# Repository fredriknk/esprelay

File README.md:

# ESPRELAY -_WORK IN PROGRESS-UNTESTED_-

ESP8266 small signal relay module utilizing an [ESP-12-F](./DOCUMENTATION/esp-12f_product_specification_en.pdf) wifi module for communication and MCU, and has two 2.5-25V inputs, and a single 25v, 100ma high speed open drain output through a [TBD062003](./DOCUMENTATION/2304140030_TOSHIBA-TBD62003AFWG_C114084.pdf) DMOS transistor array ic. The three relay outputs are capable of driving around 25V 500ma. 

Thanks to [u/PricelessToolkit/ESPClicker](https://github.com/PricelessToolkit/ESPClicker) for inspiration. If you need a ready to use product you should so head over to his [store](https://www.pricelesstoolkit.com/en/projects/32-espclicker-0741049314405.html) and buy his version.

[Schematic](./DOCUMENTATION/_schematic.pdf)

[Assembly IBOM](https://htmlpreview.github.io/?https://raw.githubusercontent.com/fredriknk/esprelay/main/PRODUCTION/ibom.html)

## Specifications
| **Parameter**   | **Description**                                                     |
|-----------------|---------------------------------------------------------------------|
| _Input voltage_ | 5-15v                               |
| _Current_       | TBD Wifi: ##mA, Radio Off: ##mA, Deep sleep ##uA |  
| _Communication_ | 2.4ghz WIFI, Uart TTL                            |
| _Baudrate_      | 115200                                                              |
| _PCB size_      | 20x65mm                                                             |
| _PCB info_      | 1.6mm FR4, HASL lead free, 4 layer (But works with 2)               |
| _Case size_     | XxXxXmm TBD                                                         |

## Connector
| **Pin**   | **GPIO**|**Description**       |
|------------|-----|-------------------------|
|_vcc_ | -|5-15v |
|_GND_ | -|  Ground  |
|_HI1_ | GPIO4 | 2.5-25v input |
|_HI1_ | GPIO5 | 2.5-25v input |
|_HO1_ | GPIO13 | 25v 100ma open drain output |
|_R1A_ | GPIO12  | Relay 1 COM |
|_R1NC_ | GPIO12 | Relay 1 Normally Closed |
|_R1NO_ | GPIO12 | Relay 1 Normally Open |
|_R2A_ | GPIO12  | Relay 1 COM |
|_R2NO_ | GPIO12 | Relay 1 Normally Open |
|_R3A_ | GPIO12  | Relay 1 COM |
|_R3NO_ | GPIO12 | Relay 1 Normally Open |

## PCB Pictures

## Homeassistant Implementation
TODO

## FIRST PRODUCTION PROTOTYPE
TODO

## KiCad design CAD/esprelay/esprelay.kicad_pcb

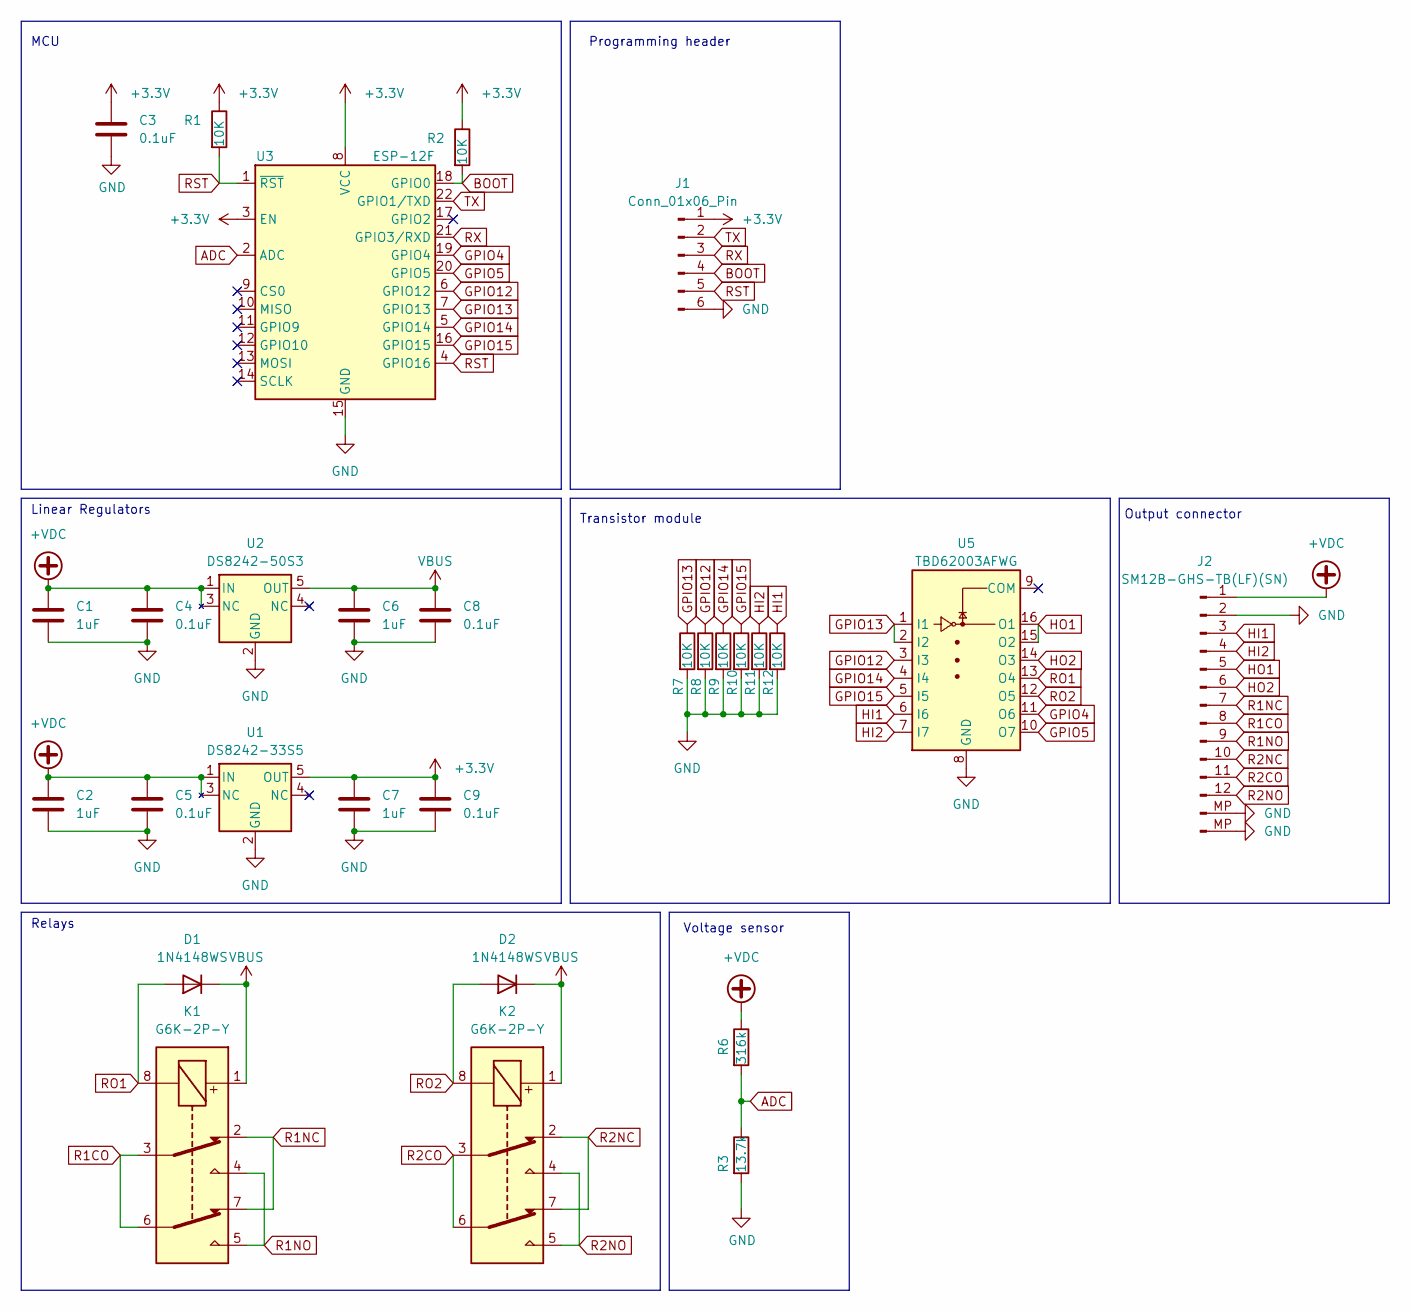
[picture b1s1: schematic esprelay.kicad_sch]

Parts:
C1, C2, C6, C7: 1uF; C_0402_1005Metric; LCSC Part # C52923
C3, C4, C5, C8, C9: 0.1uF; C_0402_1005Metric; LCSC Part # C307331
D1, D2: 1N4148WS; D_SOD-323; LCSC Part # C2128
J1: Conn_01x06_Pin; TestPoint_Pad_1.0x1.0mm_6pad
J2: SM12B-GHS-TB(LF)(SN); JST_GH_SM12B-GHS-TB_1x12-1MP_P1.25mm_Horizontal; LCSC Part # C265421
K1, K2: G6K-2P-Y; Relay_DPDT_Omron_G6K-2P-Y; LCSC Part # C80087
R1, R2, R7, R8, R9, R10, R11, R12: 10K; R_0402_1005Metric; LCSC Part # C25744
R3: 13.7k; R_0402_1005Metric; LCSC Part # C25854
R6: 316k; R_0402_1005Metric; LCSC Part # C25777
U1: DS8242-33S5; SOT-23-5; LCSC Part # C5884133
U2: DS8242-50S3; SOT-23-5; LCSC Part # C5884139
U3: ESP-12F; ESP-12E; LCSC Part # C82891
U5: TBD62003AFWG; SOIC-16_3.9x9.9mm_P1.27mm; LCSC Part # C114084

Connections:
+3.3V: C3.1, C7.1, C9.1, J1.1, R1.1, R2.1, U1.5 (OUT), U3.3 (EN), U3.8 (VCC)
+VDC: C1.1, C2.1, C4.2, C5.2, J2.1, R6.1, U1.1 (IN), U1.3 (NC), U2.1 (IN), U2.3 (NC)
ADC: R3.1, R6.2, U3.2 (ADC)
BOOT: J1.4, R2.2, U3.18 (GPIO0)
GND: C1.2, C2.2, C3.2, C4.1, C5.1, C6.2, C7.2, C8.2, C9.2, J1.6, J2.2, J2.MP (Pin_13), R3.2, R7.2, R8.2, R9.2, R10.2, R11.2, R12.2, U1.2 (GND), U2.2 (GND), U3.15 (GND), U5.8 (GND)
GPIO4: U3.19 (GPIO4), U5.11 (O6)
GPIO5: U3.20 (GPIO5), U5.10 (O7)
GPIO12: R8.1, U3.6 (GPIO12), U5.3 (I3)
GPIO13: R7.1, U3.7 (GPIO13), U5.1 (I1), U5.2 (I2)
GPIO14: R9.1, U3.5 (GPIO14), U5.4 (I4)
GPIO15: R10.1, U3.16 (GPIO15), U5.5 (I5)
HI1: J2.3, R12.1, U5.6 (I6)
HI2: J2.4, R11.1, U5.7 (I7)
HO1: J2.5, U5.15 (O2), U5.16 (O1)
HO2: J2.6, U5.14 (O3)
R1CO: J2.8, K1.3, K1.6
R1NC: J2.7, K1.2, K1.7
R1NO: J2.9, K1.4, K1.5
R2CO: J2.11, K2.3, K2.6
R2NC: J2.10, K2.2, K2.7
R2NO: J2.12, K2.4, K2.5
RO1: D1.2 (A), K1.8, U5.13 (O4)
RO2: D2.2 (A), K2.8, U5.12 (O5)
RST: J1.5, R1.2, U3.1 (~RST), U3.4 (GPIO16)
RX: J1.3, U3.21 (GPIO3/RXD)
TX: J1.2, U3.22 (GPIO1/TXD)
VBUS: C6.1, C8.1, D1.1 (K), D2.1 (K), K1.1, K2.1, U2.5 (OUT)

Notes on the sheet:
Transistor module
Linear Regulators
MCU
Output connector
Programming header
Relays
Voltage sensor

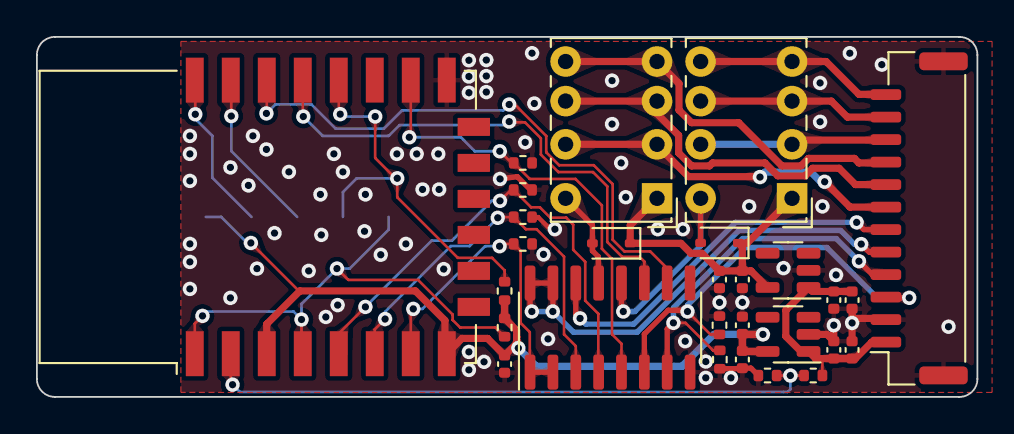
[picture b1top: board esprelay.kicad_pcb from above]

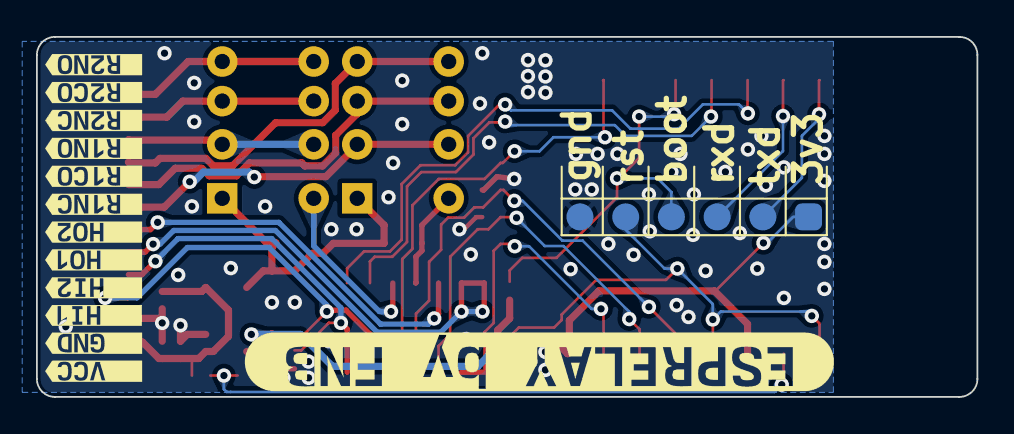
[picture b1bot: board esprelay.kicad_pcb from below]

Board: 2 copper layers, 52.2 x 20.0 mm, 42 parts (14 on the bottom side), 27 nets.

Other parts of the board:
kibuzzard-65CFDA91: G***; kibuzzard-65CFDA91
kibuzzard-65CFDAA0: G***; kibuzzard-65CFDAA0
kibuzzard-65CFDAA7: G***; kibuzzard-65CFDAA7
kibuzzard-65CFDAAD: G***; kibuzzard-65CFDAAD
kibuzzard-65CFDAB5: G***; kibuzzard-65CFDAB5
kibuzzard-65CFDABC: G***; kibuzzard-65CFDABC
kibuzzard-65666C6B: G***; kibuzzard-65666C6B
kibuzzard-65666C7B: G***; kibuzzard-65666C7B
kibuzzard-65666C71: G***; kibuzzard-65666C71
kibuzzard-65666C76: G***; kibuzzard-65666C76
kibuzzard-65666C87: G***; kibuzzard-65666C87
kibuzzard-65666CB7: G***; kibuzzard-65666CB7
kibuzzard-6566713E: G***; kibuzzard-6566713E

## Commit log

2023-11-24 Feat: Changed module to ESP12F
2023-11-27 Feat: Started Routing
2023-11-28 Feat: Pretty much complete
2023-11-28 Feat: Fixed lcsc product numbers
2023-11-28 Feat: Finished silkscreen
2023-11-28 Fix: Minor trace adjustment
2023-11-29 Feat: JLC purchase
2023-11-30 Feat: 4 layer,readme and cleanup
2023-11-30 Feat: Readme and documentation work
2023-11-30 Feat:Readme
2023-11-30 LICENSE
2023-11-30 Fix:readme
2023-12-01 Fix: Readme
2023-12-27 Added yaml file
2024-02-18 Simplification
